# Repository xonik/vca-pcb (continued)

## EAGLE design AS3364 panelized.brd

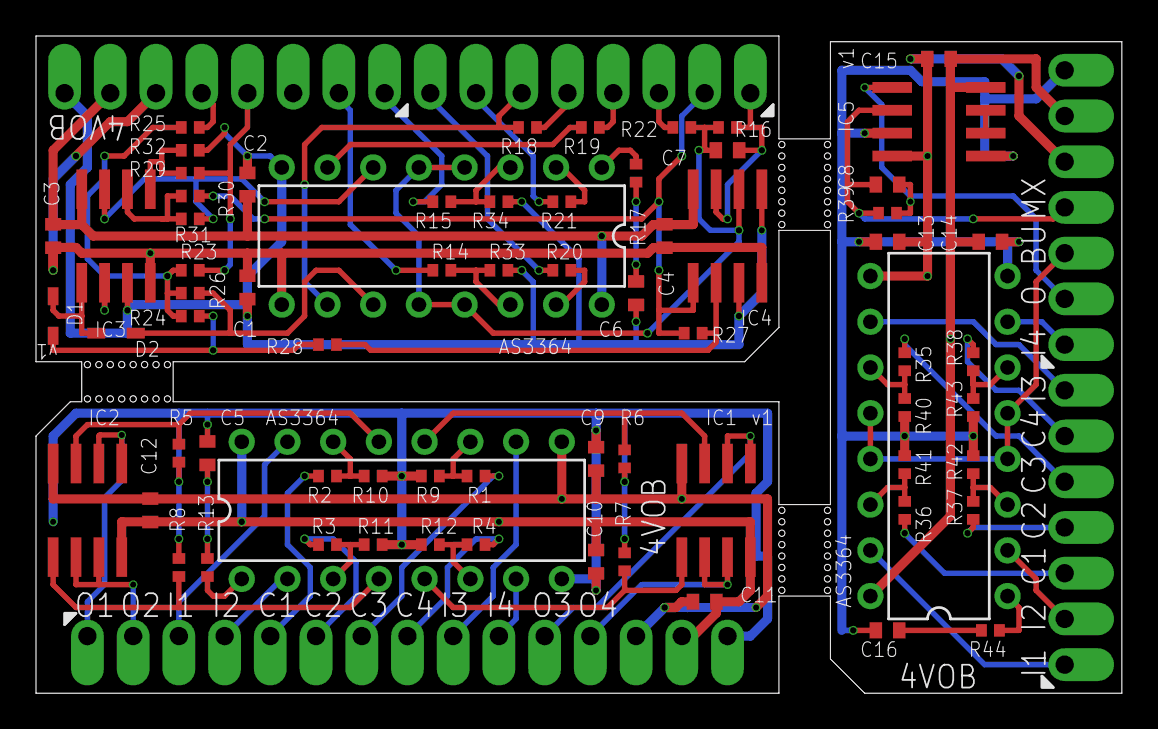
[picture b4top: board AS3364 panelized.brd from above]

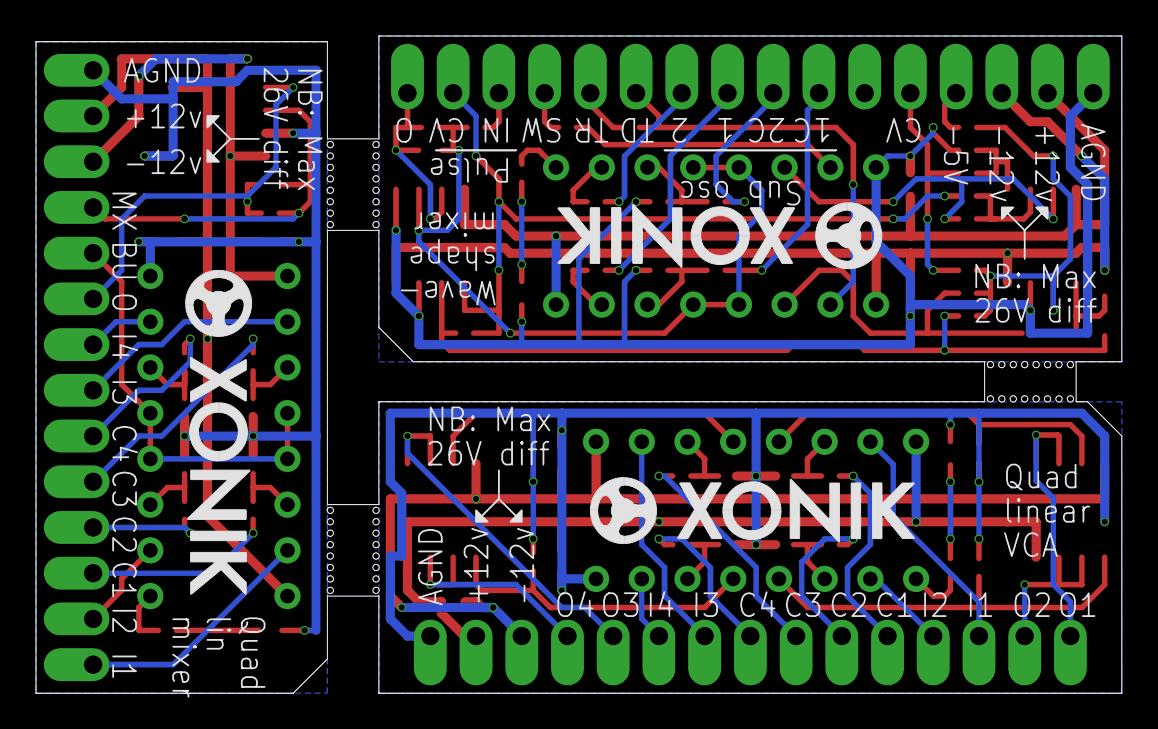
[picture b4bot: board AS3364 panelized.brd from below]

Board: 2 copper layers, 60.3 x 36.5 mm, 78 parts (3 on the bottom side), 77 nets.

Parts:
C1, C2, C3, C4, C9, C10, C11, C12, C13, C14, C15: 100nF; C0402
C5, C6, C16: 5nF; C0402
C7, C8: 33pF; C0402
D1, D2: SOD323J
DA1, DA2, DA3: AS3364D; DIL16J
IC1, IC2, IC3, IC4, IC5: TL072JD; SO08J
R1, R2, R3, R4, R14, R15, R35, R36, R37, R38: 33k; R0402
R5, R6, R7, R8, R16, R18, R19, R20, R21, R22, R39: 47k; R0402
R9, R10, R11, R12, R33, R34, R40, R41, R42, R43: 22k; R0402
R13, R17, R44: 100R; R0402
R23, R27, R29, R30: 25k; R0402
R24, R26, R31, R32: 20k; R0402
R25: 50k; R0402
R28: 10k; R0402
SV1: SIP-PIN15-1J
SV2, SV3: SIP-PIN08-1J
U$1, U$2, U$3: XONIK_LOGO_18
U$4, U$5: MA07-1JP; SIP-PIN07-1J

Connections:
+12V: C10.2, C11.2, C12.2, DA2.16, IC1.8, IC2.8, SV1.14
+12V1: C2.2, C3.2, C4.2, DA1.16, IC3.8, IC4.8, SV3.7
+12V2: C14.2, C15.2, DA3.16, IC5.8, U$4.6
-5V: R25.1, SV3.5
-12V: C9.1, C11.1, C12.1, DA2.9, IC1.4, IC2.4, SV1.13
-12V1: C1.1, C3.1, C4.1, DA1.9, IC3.4, IC4.4, SV3.6
-12V2: C13.1, C15.1, DA3.9, IC5.4, U$4.5
BUS: DA3.4, DA3.5, DA3.12, DA3.13, U$4.3
CV1: R2.1, SV1.5
CV2: R3.1, SV1.6
CV2_IN: DA2.3, R3.2, R11.2
CV2_IN1: DA3.3, R37.2, R42.2
CV3: R1.1, SV1.7
CV4: R4.1, SV1.8
CV5: R36.1, U$5.3
CV6: R35.1, U$5.5
CV7: R38.1, U$5.6
CV8: R37.1, U$5.4
GND: C5.1, C9.2, C10.1, DA2.8, R5.1, R6.1, R7.1, R8.1, R9.1, R10.1, R11.1, R12.1, SV1.15
GND1: C1.2, C2.1, C6.1, DA1.8, IC3.3, IC4.3, IC4.5, R32.1, R33.1, R34.1, SV3.8
GND2: C13.2, C14.1, C16.1, DA3.8, IC5.3, IC5.5, R40.1, R41.1, R42.1, R43.1, U$4.7
IN1: DA2.15, SV1.3
IN2: DA2.2, SV1.4
IN3: DA2.10, SV1.9
IN4: DA2.7, SV1.10
IN5: DA3.10, U$5.7
IN6: DA3.7, U$4.1
IN7: DA3.2, U$5.2
IN8: DA3.15, U$5.1
MIX: C8.1, IC5.2, R39.1, U$4.4
MIX_BUS: C7.2, DA1.4, DA1.5, DA1.12, DA1.13, IC4.6, R16.2, R22.1
unnamed: DA1.1, R17.2
unnamed: DA2.1, R13.2
unnamed: C6.2, R17.1
unnamed: DA2.4, IC2.5, R8.2
unnamed: IC3.5, R29.2, R32.2
unnamed: DA2.5, IC1.5, R7.2
unnamed: D1.1, D2.2, IC3.1
unnamed: IC3.2, R23.2, R24.1, R25.2, R26.1
unnamed: DA3.1, R44.2
unnamed: DA2.6, R4.2, R12.2
unnamed: DA2.12, IC1.3, R6.2
unnamed: DA2.11, R1.2, R9.2
unnamed: DA2.13, IC2.3, R5.2
unnamed: C5.2, R13.1
unnamed: IC3.6, R30.2, R31.1
unnamed: DA3.6, R38.2, R43.2
unnamed: DA3.11, R35.2, R40.2
unnamed: IC4.2, R27.1, R28.2
unnamed: D1.2, R24.2, R28.1
unnamed: DA3.14, R36.2, R41.2
unnamed: DA2.14, R2.2, R10.2
unnamed: C16.2, R44.1
NC1: IC5.6, IC5.7
OUT: C7.1, IC4.7, R16.1, SV2.1
OUT1: IC2.1, IC2.2, SV1.1
OUT2: IC2.6, IC2.7, SV1.2
OUT3: IC1.1, IC1.2, SV1.11
OUT4: IC1.6, IC1.7, SV1.12
OUT5: C8.2, IC5.1, R39.2, U$4.2
PAN_CV: R23.1, R29.1, SV3.4
PULSE_CV: IC4.1, R27.2, R30.1, SV2.2
PULSE_IN: R22.2, SV2.3
SAW: R19.1, SV2.4
SAW_CV: DA1.6, IC3.7, R31.2
SAW_IN: DA1.7, R19.2
SUB1: R20.1, SV2.8
SUB1_CV: R14.1, SV3.2
SUB1_CV_IN: DA1.14, R14.2, R33.2
SUB1_IN: DA1.15, R20.2
SUB2: R21.1, SV2.7
SUB2_CV: R15.1, SV3.1
SUB2_CV_IN: DA1.3, R15.2, R34.2
SUB2_IN: DA1.2, R21.2
TRI: R18.1, SV2.5
TRI_CV: D2.1, DA1.11, R26.2
TRI_IN: DA1.10, R18.2, SV2.6

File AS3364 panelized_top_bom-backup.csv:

Comment,Designator,Footprint,LCSC Part #
5nF,C5 C6 C16,C0402,C1538
1N4148,D1 D2,SOD323J,C2128
10k,R28,R0402,C25744
20k,R24 R26 R31 R32,R0402,C25765
22k,R9 R10 R11 R12 R33 R34 R40 R41 R42 R43,R0402,C25768
25k,R23 R27 R29 R30,R0402,C25874
33k,R1 R2 R3 R4 R14 R15 R35 R36 R37 R38,R0402,C25779
33pF,C7 C8,C0402,C1562
47k,R5 R6 R7 R8 R16 R18 R19 R20 R21 R22 R39,R0402,C25792
50k,R25,R0402,C25897
100R,R13 R17 R44,R0402,C25076
100nF,C1 C2 C3 C4 C9 C10 C11 C12 C13 C14 C15,C0402,C307331
TL072,IC1 IC2 IC3 IC4 IC5,SO08,C6961
